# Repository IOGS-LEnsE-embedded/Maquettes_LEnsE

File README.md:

# LEnsE IOGS Maquettes
Maquettes pédagogiques du LEnsE / IOGS / France
2023

## A propos de l'Institut d'Optique et du LEnsE
Le **LEnsE**, ***Laboratoire d'Enseignement Expérimental***, forme au métier de l’ingénieur en photonique par la pratique : travaux pratiques, projets encadrés… Pour plus d'informations sur cette structure, dépendante de l'Institut d'Optique Graduate School, vous pouvez visiter le site officiel : [Site du LEnsE](http://lense.institutoptique.fr/)

## Maquettes pédagogiques
Le personnel du LEnsE développe des maquettes pédagogiques utilisées dans les différents travaux pratiques et projets proposés aux élèves de l'Institut d'Optique. 

Nous mettons ici à disposition l'ensemble des documents permettant la **reproduction de ces maquettes**, à savoir les plans des cartes électroniques (format Kicad et Gerber), les programmes de test et une documentation. Lorsque la maquette s'y prête, vous pourrez également trouver un sujet de TP pour des élèves de Licence à Master.

Les maquettes sont triées selon les **catégories suivantes** :

- Electronique analogique (répertoire *Elec\_Analog* )
- Electronique numérique / embarquée (répertoire *Elec\_Num\_Emb* )

## Utilisation
Vous trouverez dans les différents répertoires des maquettes, les éléments suivants (selon la nature de la maquette) :

- répertoire **carte** : le projet Kicad (schéma, PCB) et les fichiers gerber associés
- document **brochage** : le brochage de la carte (format PDF et PPTX)
- document **documentation** : une notice d'utilisation de la maquette
- répertoire **progs** : des programmes de tests (dans le cas de maquettes pour l'électronique embarquée)

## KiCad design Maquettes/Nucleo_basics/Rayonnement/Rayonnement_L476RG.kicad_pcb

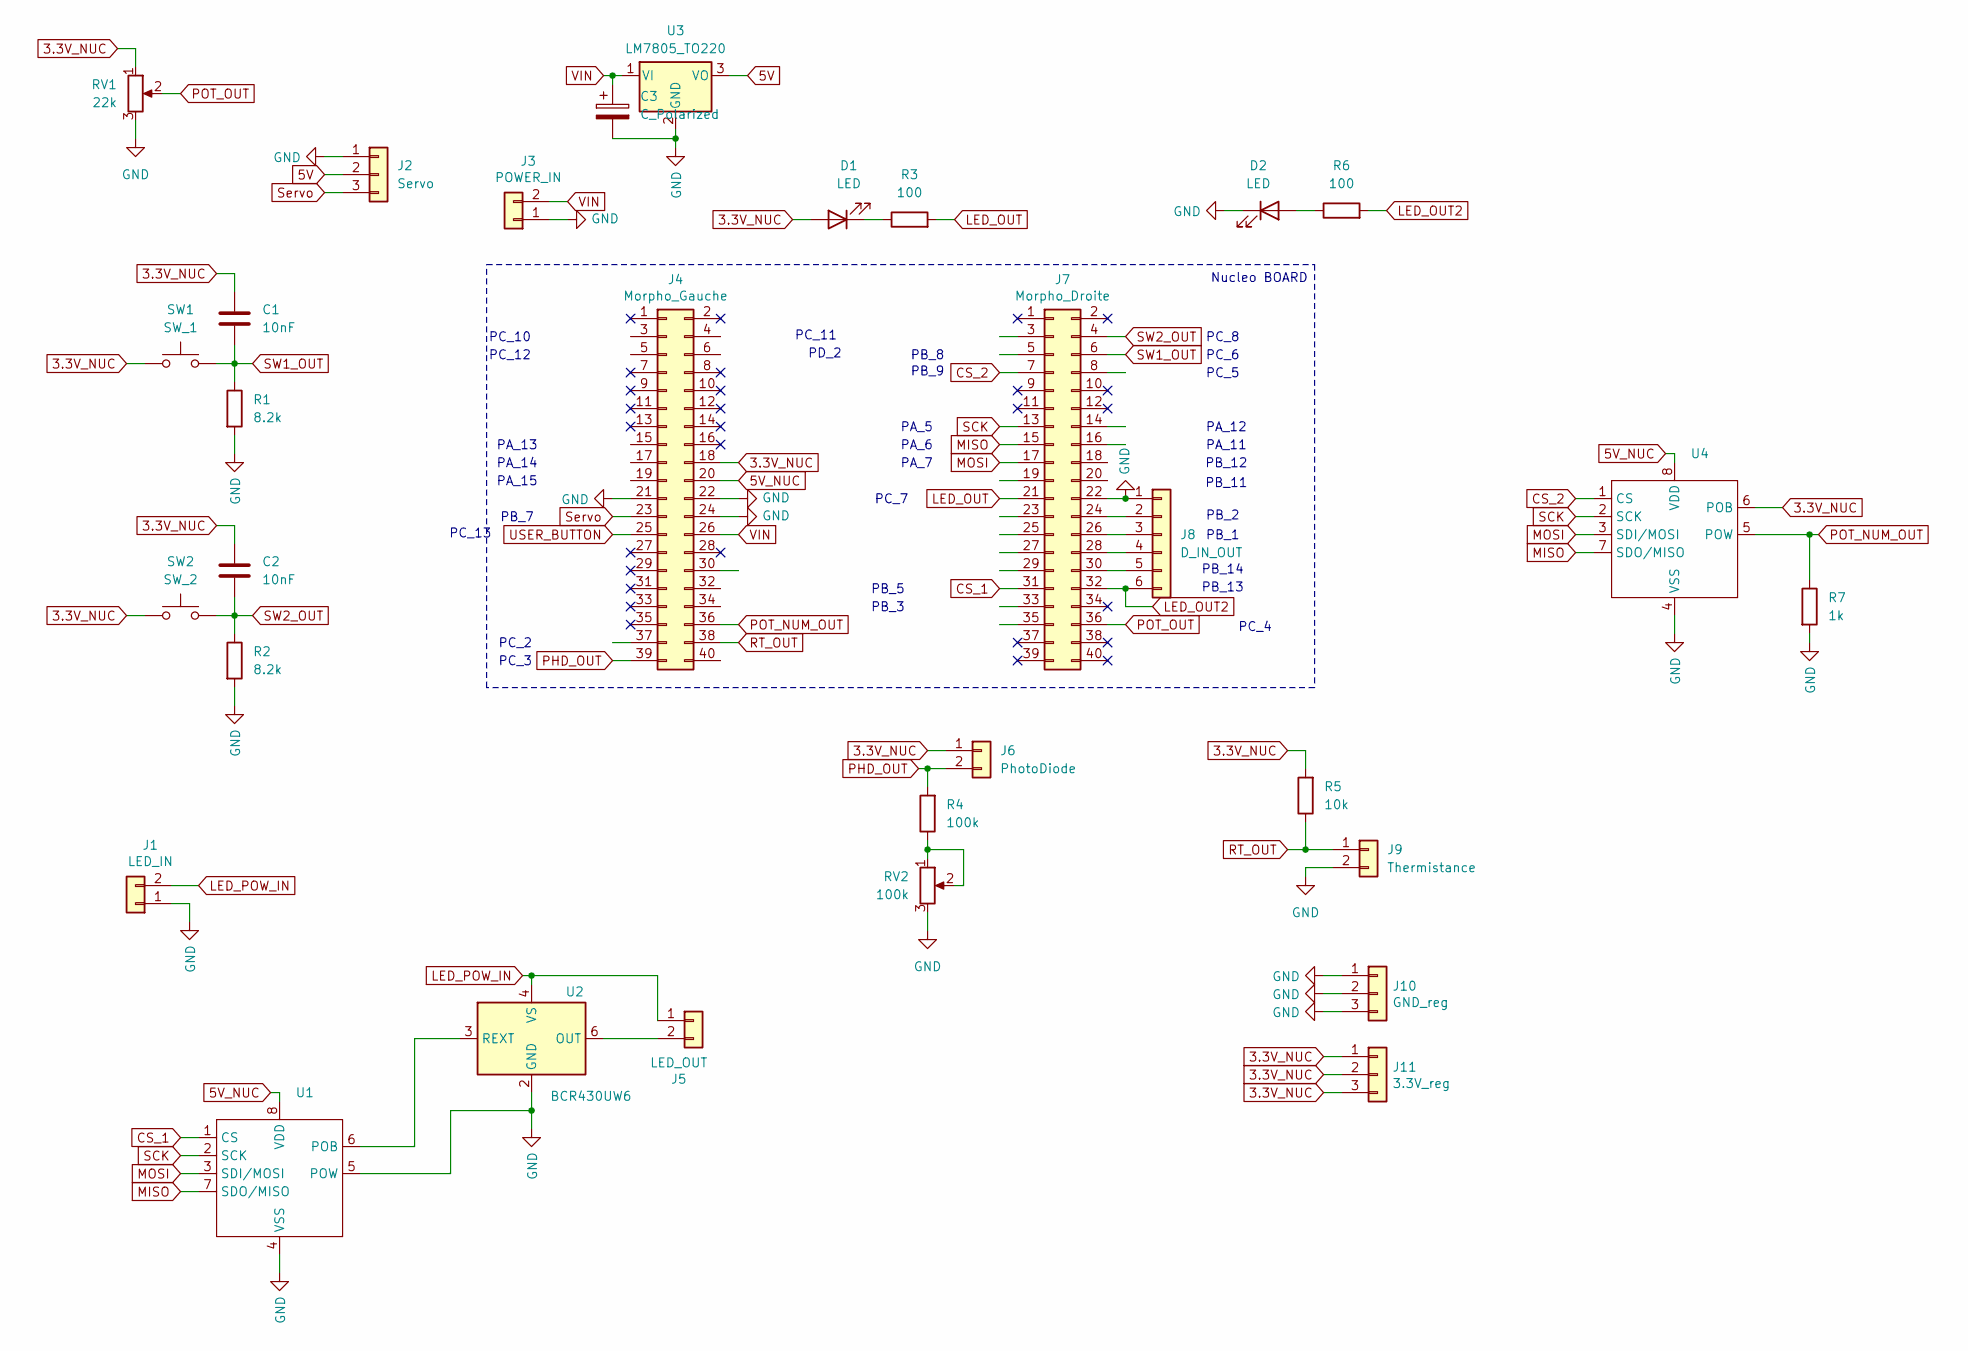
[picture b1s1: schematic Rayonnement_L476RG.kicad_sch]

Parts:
C1, C2: 10nF; C_Rect_L7.0mm_W3.5mm_P5.00mm
C3: C_Polarized; CP_Radial_D6.3mm_P2.50mm
D1, D2: LED; LED_D3.0mm_Clear
J1: LED_IN; TerminalBlock_Phoenix_MKDS-3-2-5.08_1x02_P5.08mm_Horizontal
J2: Servo; PinSocket_1x03_P2.54mm_Vertical
J3: POWER_IN; TerminalBlock_Phoenix_MKDS-3-2-5.08_1x02_P5.08mm_Horizontal
J4: Morpho_Gauche; PinHeader_2x20_P2.54mm_Vertical
J5: LED_OUT; TerminalBlock_Phoenix_MKDS-3-2-5.08_1x02_P5.08mm_Horizontal
J6: PhotoDiode; PinHeader_1x02_P2.54mm_Vertical
J7: Morpho_Droite; PinHeader_2x20_P2.54mm_Vertical
J8: D_IN_OUT; PinSocket_1x06_P2.54mm_Vertical
J9: Thermistance; PinHeader_1x02_P2.54mm_Vertical
J10: GND_reg; PinHeader_1x03_P2.54mm_Vertical
J11: 3.3V_reg; PinHeader_1x03_P2.54mm_Vertical
R1, R2: 8.2k; R_Axial_DIN0207_L6.3mm_D2.5mm_P10.16mm_Horizontal
R3, R6: 100; R_Axial_DIN0207_L6.3mm_D2.5mm_P10.16mm_Horizontal
R4: 100k; R_Axial_DIN0207_L6.3mm_D2.5mm_P10.16mm_Horizontal
R5: 10k; R_Axial_DIN0207_L6.3mm_D2.5mm_P10.16mm_Horizontal
R7: 1k; R_Axial_DIN0207_L6.3mm_D2.5mm_P10.16mm_Horizontal
RV1: 22k; Potentiometer_Bourns_3386P_Vertical
RV2: 100k; Potentiometer_Bourns_3386P_Vertical
SW1: SW_1; Switch
SW2: SW_2; Switch
U1, U4: DIP-8_W7.62mm_LongPads
U2: BCR430UW6; SC-74-6_1.55x2.9mm_P0.95mm
U3: LM7805_TO220; TO-220-3_Vertical

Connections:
3.3V_NUC: C1.1, C2.1, D1.2 (A), J4.18, J6.1, J11.1, J11.2, J11.3, R5.2, RV1.1, SW1.1, SW2.1, U4.6 (POB)
5V: J2.2, U3.3 (VO)
5V_NUC: J4.20, U1.8 (VDD), U4.8 (VDD)
CS_1: J7.31, U1.1 (CS)
CS_2: J7.7, U4.1 (CS)
GND: C3.2, D2.1 (K), J1.1, J2.1, J3.1, J4.21, J4.22, J4.24, J7.22, J8.1, J9.2, J10.1, J10.2, J10.3, R1.2, R2.2, R7.2, RV1.3, RV2.3, U1.4 (VSS), U1.5 (POW), U2.2 (GND), U3.2 (GND), U4.4 (VSS)
LED_OUT: J7.21, R3.2
LED_OUT2: J7.32, J8.6, R6.2
LED_POW_IN: J1.2, J5.1, U2.4 (VS)
MISO: J7.15, U1.7 (SDO/MISO), U4.7 (SDO/MISO)
MOSI: J7.17, U1.3 (SDI/MOSI), U4.3 (SDI/MOSI)
unnamed: D1.1 (K), R3.1
unnamed: D2.2 (A), R6.1
unnamed: J5.2, U2.6 (OUT)
unnamed: J7.24, J8.2
unnamed: J7.26, J8.3
unnamed: J7.28, J8.4
unnamed: J7.30, J8.5
unnamed: R4.1, RV2.1, RV2.2
unnamed: U1.6 (POB), U2.3 (REXT)
PHD_OUT: J4.39, J6.2, R4.2
POT_NUM_OUT: J4.36, R7.1, U4.5 (POW)
POT_OUT: J7.36, RV1.2
RT_OUT: J4.38, J9.1, R5.1
SCK: J7.13, U1.2 (SCK), U4.2 (SCK)
SW1_OUT: C1.2, J7.6, R1.1, SW1.2
SW2_OUT: C2.2, J7.4, R2.1, SW2.2
Servo: J2.3, J4.23
USER_BUTTON: J4.25
VIN: C3.1, J3.2, J4.26, U3.1 (VI)

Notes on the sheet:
PA_12
PC_2
PB_8
PA_7
PC_8
PC_11
PB_3
PA_5
PB_13
PA_14
PB_11
PC_7
PB_9
PC_5
PB_2
PC_12
PB_14
PC_13
PD_2
PA_15
PC_10
PA_11
PC_4
PA_6
PA_13
PB_7
Nucleo BOARD
PB_12
PC_3
PB_1
PC_6
PB_5

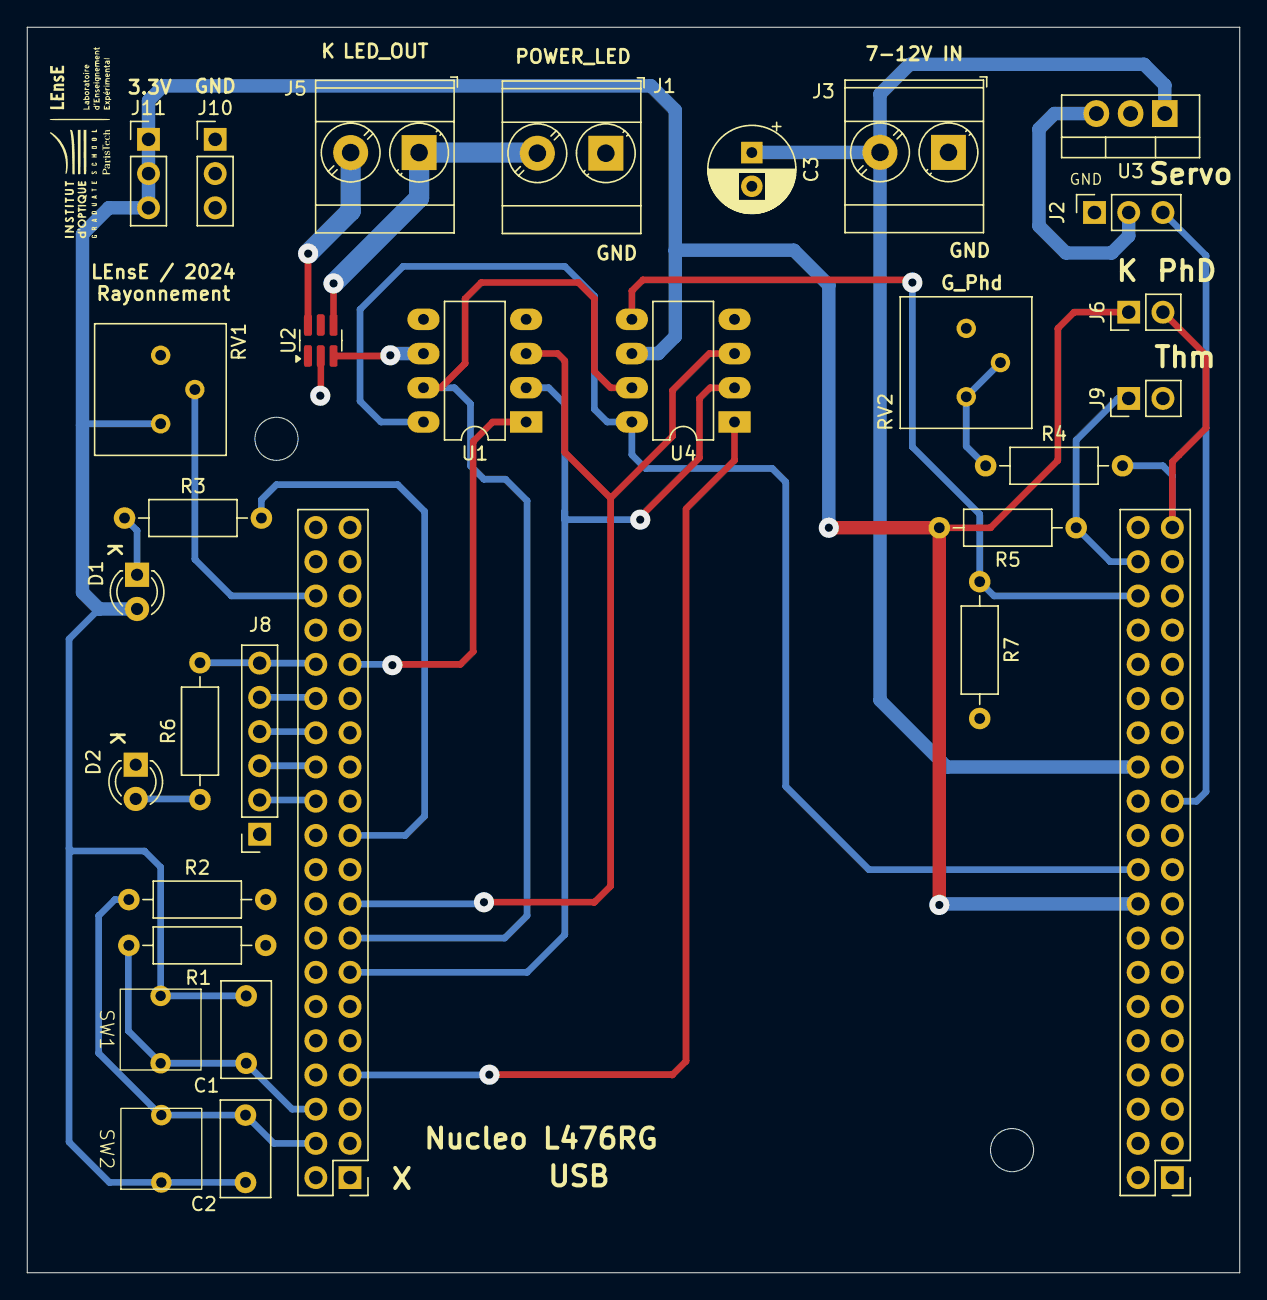
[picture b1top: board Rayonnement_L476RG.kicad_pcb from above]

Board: 2 copper layers, 90.0 x 92.5 mm, 31 parts (0 on the bottom side), 29 nets.

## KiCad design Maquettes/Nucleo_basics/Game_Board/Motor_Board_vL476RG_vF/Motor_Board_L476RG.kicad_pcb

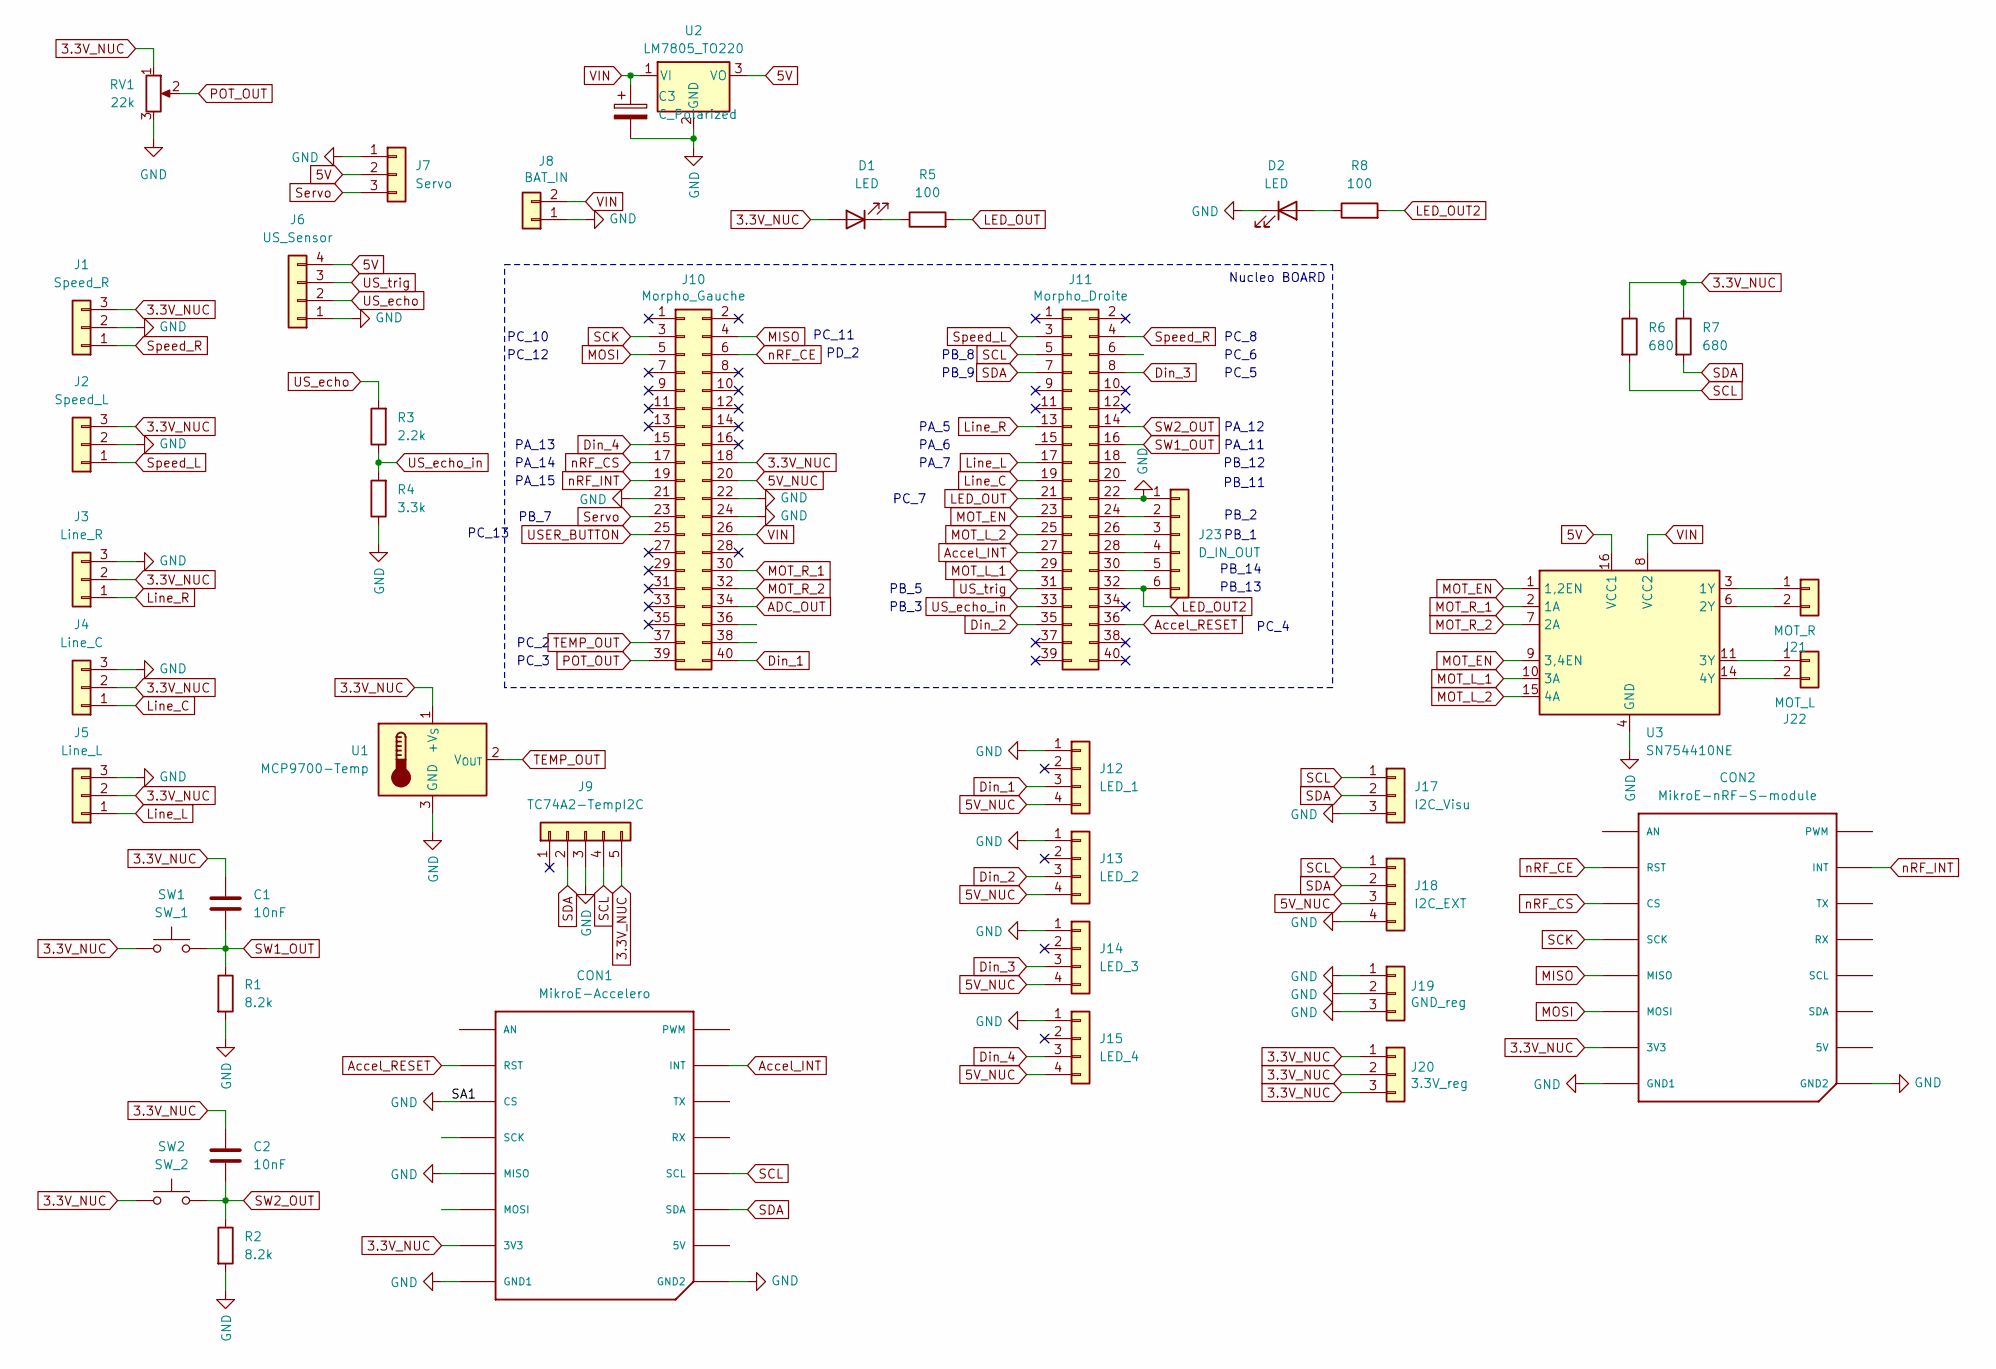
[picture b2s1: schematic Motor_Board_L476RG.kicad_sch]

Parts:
C1, C2: 10nF; C_Rect_L7.0mm_W3.5mm_P5.00mm
C3: C_Polarized; CP_Radial_D6.3mm_P2.50mm
CON1: MikroE-Accelero; MIKROBUS_MODULE_CONN
CON2: MikroE-nRF-S-module; MIKROBUS_MODULE_CONN
D1, D2: LED; LED_D3.0mm_Clear
J1: Speed_R; PinSocket_1x03_P2.54mm_Horizontal
J2: Speed_L; PinSocket_1x03_P2.54mm_Horizontal
J3: Line_R; PinSocket_1x03_P2.54mm_Horizontal
J4: Line_C; PinSocket_1x03_P2.54mm_Horizontal
J5: Line_L; PinSocket_1x03_P2.54mm_Horizontal
J6: US_Sensor; PinSocket_1x04_P2.54mm_Vertical
J7: Servo; PinSocket_1x03_P2.54mm_Horizontal
J8: BAT_IN; TerminalBlock_Phoenix_MKDS-3-2-5.08_1x02_P5.08mm_Horizontal
J9: TC74A2-TempI2C; TO-220-5_Vertical
J10: Morpho_Gauche; PinHeader_2x20_P2.54mm_Vertical
J11: Morpho_Droite; PinHeader_2x20_P2.54mm_Vertical
J12: LED_1; PinSocket_1x04_P2.54mm_Horizontal
J13: LED_2; PinSocket_1x04_P2.54mm_Horizontal
J14: LED_3; PinSocket_1x04_P2.54mm_Horizontal
J15: LED_4; PinSocket_1x04_P2.54mm_Horizontal
J17: I2C_Visu; PinSocket_1x03_P2.54mm_Vertical
J18: I2C_EXT; PinSocket_1x04_P2.54mm_Vertical
J19: GND_reg; PinHeader_1x03_P2.54mm_Vertical
J20: 3.3V_reg; PinHeader_1x03_P2.54mm_Vertical
J21: MOT_R; TerminalBlock_Phoenix_MKDS-3-2-5.08_1x02_P5.08mm_Horizontal
J22: MOT_L; TerminalBlock_Phoenix_MKDS-3-2-5.08_1x02_P5.08mm_Horizontal
J23: D_IN_OUT; PinSocket_1x06_P2.54mm_Vertical
R1, R2: 8.2k; R_Axial_DIN0207_L6.3mm_D2.5mm_P10.16mm_Horizontal
R3: 2.2k; R_Axial_DIN0207_L6.3mm_D2.5mm_P10.16mm_Horizontal
R4: 3.3k; R_Axial_DIN0207_L6.3mm_D2.5mm_P10.16mm_Horizontal
R5, R8: 100; R_Axial_DIN0207_L6.3mm_D2.5mm_P10.16mm_Horizontal
R6, R7: 680; R_Axial_DIN0207_L6.3mm_D2.5mm_P10.16mm_Horizontal
RV1: 22k; Potentiometer_Bourns_3386P_Vertical
SW1: SW_1; Switch
SW2: SW_2; Switch
U1: MCP9700-Temp; TO-92_Inline
U2: LM7805_TO220; TO-220-3_Vertical
U3: SN754410NE; DIP-16_W7.62mm

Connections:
3.3V_NUC: C1.1, C2.1, CON1.P7 (3V3), CON2.P7 (3V3), D1.2 (A), J1.3, J2.3, J3.2, J4.2, J5.2, J9.5, J10.18, J20.1, J20.2, J20.3, R6.1, R7.1, RV1.1, SW1.1, SW2.1, U1.1 (+V_{S})
5V: J6.4, J7.2, U2.3 (VO), U3.16 (VCC1)
5V_NUC: J10.20, J12.4, J13.4, J14.4, J15.4, J18.3
ADC_OUT: J10.34
Accel_INT: CON1.P15 (INT), J11.27
Accel_RESET: CON1.P2 (RST), J11.36
Din_1: J10.40, J12.3
Din_2: J11.35, J13.3
Din_3: J11.8, J14.3
Din_4: J10.15, J15.3
GND: C3.2, CON1.P3 (CS), CON1.P5 (MISO), CON1.P8 (GND1), CON1.P9 (GND2), CON2.P8 (GND1), CON2.P9 (GND2), D2.1 (K), J1.2, J2.2, J3.3, J4.3, J5.3, J6.1, J7.1, J8.1, J9.3, J10.21, J10.22, J10.24, J11.22, J12.1, J13.1, J14.1, J15.1, J17.3, J18.4, J19.1, J19.2, J19.3, J23.1, R1.2, R2.2, R4.1, RV1.3, U1.3 (GND), U2.2 (GND), U3.4 (GND), U3.5 (GND), U3.12 (GND), U3.13 (GND)
LED_OUT: J11.21, R5.2
LED_OUT2: J11.32, J23.6, R8.2
Line_C: J4.1, J11.19
Line_L: J5.1, J11.17
Line_R: J3.1, J11.13
MISO: CON2.P5 (MISO), J10.4
MOSI: CON2.P6 (MOSI), J10.5
MOT_EN: J11.23, U3.1 (1,2EN), U3.9 (3,4EN)
MOT_L_1: J11.29, U3.10 (3A)
MOT_L_2: J11.25, U3.15 (4A)
MOT_R_1: J10.30, U3.2 (1A)
MOT_R_2: J10.32, U3.7 (2A)
unnamed: D1.1 (K), R5.1
unnamed: D2.2 (A), R8.1
unnamed: J11.24, J23.2
unnamed: J11.26, J23.3
unnamed: J11.28, J23.4
unnamed: J11.30, J23.5
unnamed: J21.1, U3.3 (1Y)
unnamed: J21.2, U3.6 (2Y)
unnamed: J22.1, U3.11 (3Y)
unnamed: J22.2, U3.14 (4Y)
POT_OUT: J10.39, RV1.2
SCK: CON2.P4 (SCK), J10.3
SCL: CON1.P12 (SCL), J9.4, J11.5, J17.1, J18.1, R6.2
SDA: CON1.P11 (SDA), J9.2, J11.7, J17.2, J18.2, R7.2
SW1_OUT: C1.2, J11.16, R1.1, SW1.2
SW2_OUT: C2.2, J11.14, R2.1, SW2.2
Servo: J7.3, J10.23
Speed_L: J2.1, J11.3
Speed_R: J1.1, J11.4
TEMP_OUT: J10.37, U1.2 (V_{OUT})
USER_BUTTON: J10.25
US_echo: J6.2, R3.2
US_echo_in: J11.33, R3.1, R4.2
US_trig: J6.3, J11.31
VIN: C3.1, J8.2, J10.26, U2.1 (VI), U3.8 (VCC2)
nRF_CE: CON2.P2 (RST), J10.6
nRF_CS: CON2.P3 (CS), J10.17
nRF_INT: CON2.P15 (INT), J10.19

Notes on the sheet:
PA_12
PC_2
PB_8
PA_7
PC_8
PC_11
PB_3
PA_5
PB_13
PA_14
PB_11
PC_7
PB_9
PC_5
PB_2
PC_12
PB_14
PC_13
PD_2
PA_15
PC_10
PA_11
PC_4
PA_6
PA_13
PB_7
Nucleo BOARD
PB_12
PC_3
PB_1
PC_6
PB_5

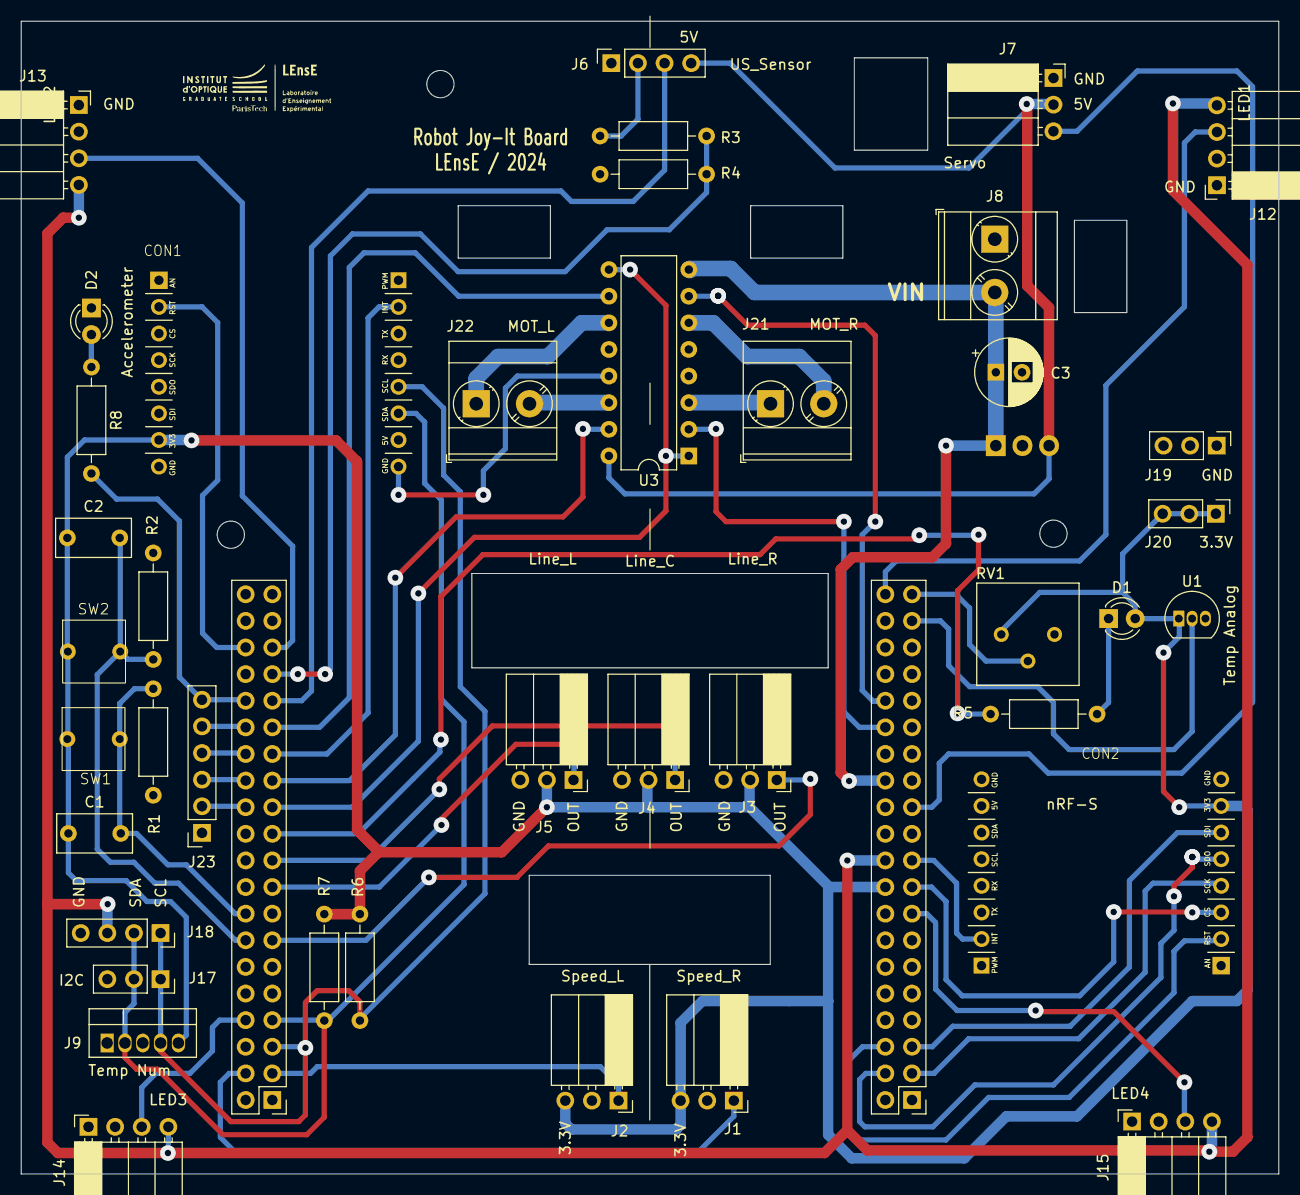
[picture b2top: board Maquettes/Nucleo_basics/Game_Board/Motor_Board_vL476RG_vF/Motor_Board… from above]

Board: 2 copper layers, 120.0 x 110.0 mm, 43 parts (1 on the bottom side), 49 nets.

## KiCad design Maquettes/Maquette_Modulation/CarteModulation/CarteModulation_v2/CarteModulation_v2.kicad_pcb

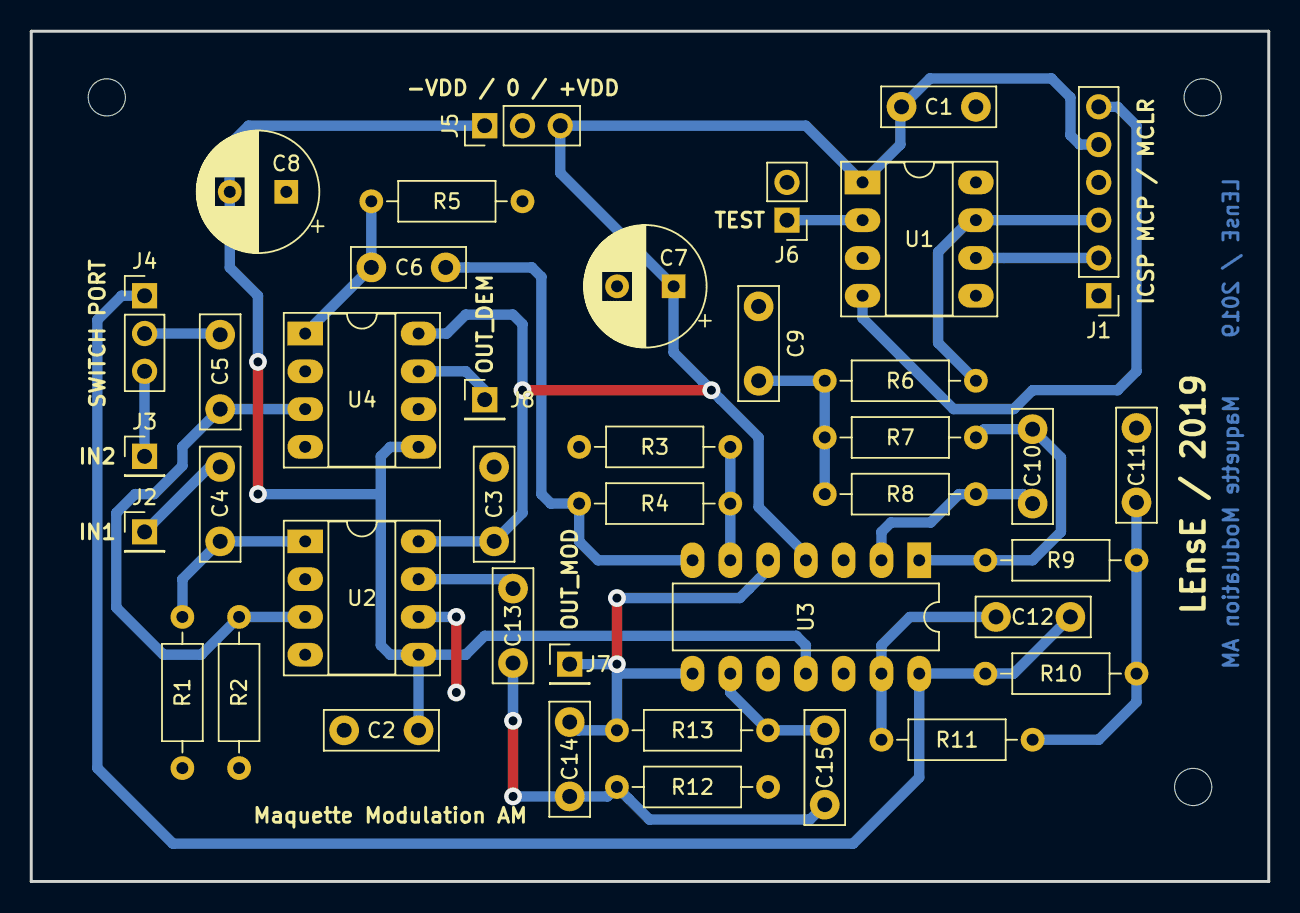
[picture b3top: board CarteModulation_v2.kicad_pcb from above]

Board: 2 copper layers, 83.2 x 57.1 mm, 41 parts (0 on the bottom side), 26 nets.

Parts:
C1, C2, C3, C4, C5, C6: 100n; C_Disc_D7.5mm_W2.5mm_P5.00mm
C7, C8: 10uF; CP_Radial_D8.0mm_P3.80mm
C9, C11: 4.7n; C_Disc_D7.5mm_W2.5mm_P5.00mm
C10, C12: 1n; C_Disc_D7.5mm_W2.5mm_P5.00mm
C13, C14, C15: 2.2n; C_Disc_D7.5mm_W2.5mm_P5.00mm
J1: ICSP; PinHeader_1x06_P2.54mm_Vertical
J2: IN1_I; PinHeader_1x01_P2.54mm_Vertical
J3: IN2_I; PinHeader_1x01_P2.54mm_Vertical
J4: CHOIX_IN; PinHeader_1x03_P2.54mm_Vertical
J5: ALIM; PinHeader_1x03_P2.54mm_Vertical
J6: TEST; PinHeader_1x02_P2.54mm_Vertical
J7: OUT_MOD; PinHeader_1x01_P2.54mm_Vertical
J8: OUT_DEMODU; PinHeader_1x01_P2.54mm_Vertical
R1, R2, R5: 100k; R_Axial_DIN0207_L6.3mm_D2.5mm_P10.16mm_Horizontal
R3, R12: 2.7k; R_Axial_DIN0207_L6.3mm_D2.5mm_P10.16mm_Horizontal
R4, R13: 27k; R_Axial_DIN0207_L6.3mm_D2.5mm_P10.16mm_Horizontal
R6, R9: 3.9k; R_Axial_DIN0207_L6.3mm_D2.5mm_P10.16mm_Horizontal
R7, R8, R10, R11: 3.3k; R_Axial_DIN0207_L6.3mm_D2.5mm_P10.16mm_Horizontal
U1: PIC12F1501-IP; DIP-8_W7.62mm_Socket_LongPads
U2, U4: AD633_DIP; DIP-8_W7.62mm_Socket_LongPads
U3: TL084; DIP-14_W7.62mm_LongPads
eREF**: MountingHole_2.5mm

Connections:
-VDD: C2.1, C8.2, J5.1, U2.5, U3.11, U4.5
GND: C1.1, C2.2, C3.1, C7.2, C8.1, C9.1, C11.1, J1.4, J5.2, J6.2, R1.2, R2.2, R3.2, R5.2, R12.1, U1.3, U1.8, U2.2, U2.4, U2.6, U3.3, U3.10, U3.12, U4.2, U4.4, U4.6
ICSP_MCLR: J1.6, U1.4
ICSP_PGC: J1.2, U1.6
ICSP_PGD: J1.3, R6.2, U1.7
IN1: C4.2, J2.1
IN2: J3.1, J4.3
IN2_CH: C5.2, J4.2
IN2_CH_FIL: C5.1, R2.1, U2.3, U4.3
MOD_AMP: C6.2, R4.1, U3.7
unnamed: C4.1, R1.1, U2.1
unnamed: C6.1, R5.1, U4.1
unnamed: C9.2, R6.1, R7.1, R8.2
unnamed: C10.1, R7.2, R9.2, U3.1
unnamed: C10.2, R8.1, U3.2
unnamed: C11.2, R9.1, R10.1, R11.2
unnamed: C12.2, R11.1, U3.13
unnamed: C13.1, C14.2, C15.1, R12.2
unnamed: C15.2, R13.1, U3.9
unnamed: R3.1, R4.2, U3.6
OUT2_FILT: C12.1, J4.1, R10.2, U3.14
OUT_DEMOD: J8.1, U4.7
OUT_MODUL: C14.1, J7.1, R13.2, U3.5, U3.8
OUT_MODUL_M: C13.2, U2.7
TEST_OUT: J6.1, U1.2
VDD: C1.2, C3.2, C7.1, J1.5, J5.3, U1.1, U2.8, U3.4, U4.8

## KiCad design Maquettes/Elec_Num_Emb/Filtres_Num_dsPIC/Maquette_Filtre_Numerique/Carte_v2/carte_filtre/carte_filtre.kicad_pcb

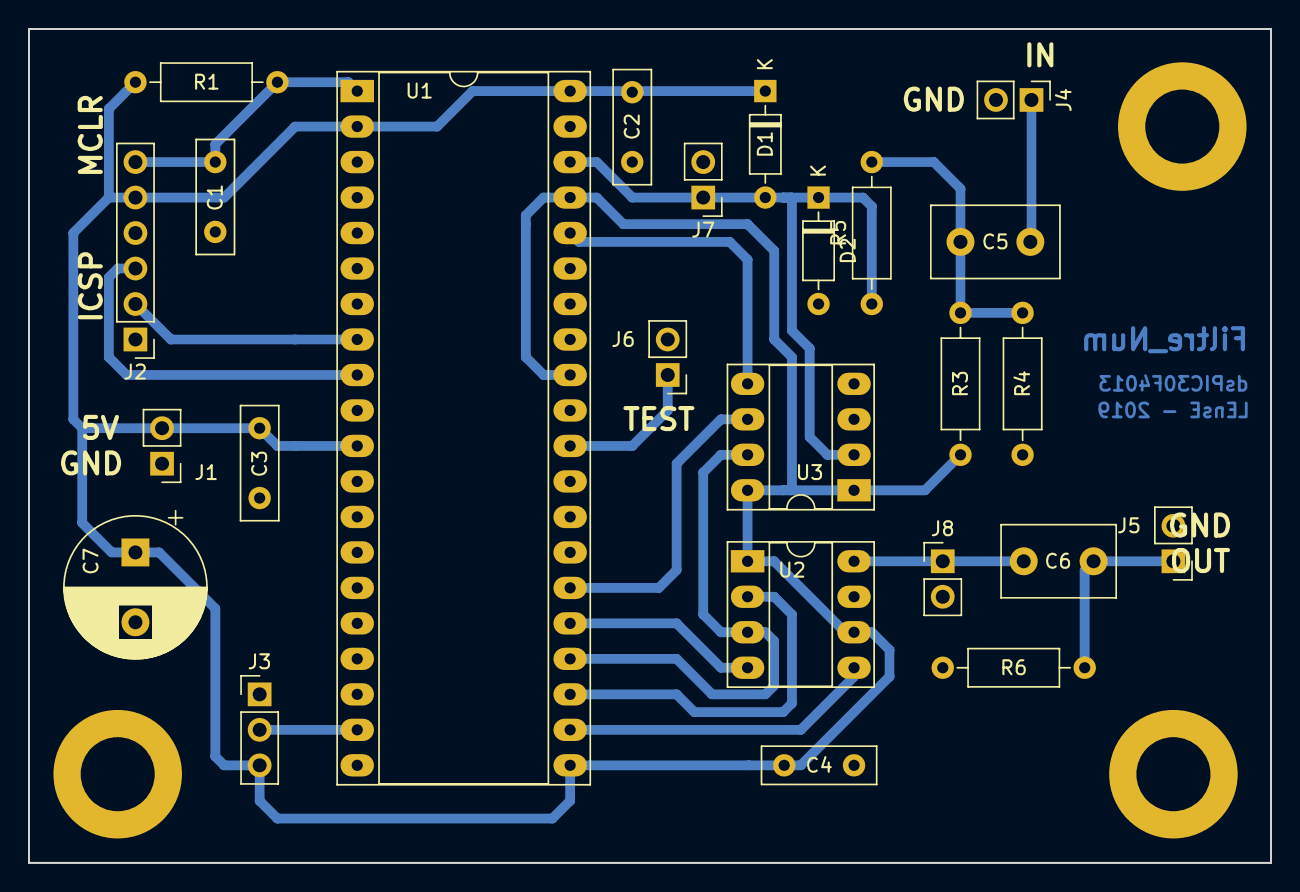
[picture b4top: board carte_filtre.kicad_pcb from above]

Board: 2 copper layers, 88.9 x 59.7 mm, 26 parts (0 on the bottom side), 18 nets.

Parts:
C1: 68pF; C_Disc_D8.0mm_W2.5mm_P5.00mm
C2, C3, C4: 100nF; C_Disc_D8.0mm_W2.5mm_P5.00mm
C5: 330nF; C_Disc_D9.0mm_W5.0mm_P5.00mm
C6: 1u; C_Disc_D8.0mm_W5.0mm_P5.00mm
C7: CP; CP_Radial_D10.0mm_P5.00mm
D1, D2: 1N4148; D_DO-35_SOD27_P7.62mm_Horizontal
H: MountingHole_5.3mm_M5_DIN965_Pad
J1: ALIM; PinHeader_1x02_P2.54mm_Vertical
J2: ICSP_MICROCHIP; PinHeader_1x06_P2.54mm_Vertical
J3: CHOIX_FILTRE_SUIVEUR; PinHeader_1x03_P2.54mm_Vertical
J4: ANALOG_IN_; PinHeader_1x02_P2.54mm_Vertical
J5: FILTERED_OUT; PinHeader_1x02_P2.54mm_Vertical
J6: TEST_OUT; PinHeader_1x02_P2.54mm_Vertical
J7: TEST_IN_; PinHeader_1x02_P2.54mm_Vertical
J8: TEST_OUT_*; PinHeader_1x02_P2.54mm_Vertical
R1, R6: 10k; R_Axial_DIN0207_L6.3mm_D2.5mm_P10.16mm_Horizontal
R3, R4: 100k; R_Axial_DIN0207_L6.3mm_D2.5mm_P10.16mm_Horizontal
R5: 1k; R_Axial_DIN0207_L6.3mm_D2.5mm_P10.16mm_Horizontal
U1: DSPIC30F3014-20E_P; DIP-40_W15.24mm_Socket_LongPads
U2: MCP4921; DIP-8_W7.62mm_Socket_LongPads
U3: MCP3201; DIP-8_W7.62mm_Socket_LongPads

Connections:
ADC_CS: U1.36, U3.5
ANALOG_IN: D1.2, D2.1, J7.1, R5.1, U1.38, U3.2
ANALOG_IN_NOT_FILTERED: C5.2, J4.1
ANALOG_OUT: C6.1, J5.1, R6.2
ANALOG_OUT_MOY: C6.2, J8.1, U2.8
CHOIX_IN: J3.2, U1.19
DAC_CS: U1.23, U2.2
DAC_LD: U1.22, U2.5
GND: C1.1, C2.2, C3.2, C4.2, C7.2, D2.2, J1.1, J2.4, J3.1, J4.2, J5.2, J6.2, J7.2, J8.2, R4.2, R6.1, U1.3, U1.12, U1.20, U1.31, U1.39, U2.7, U3.3, U3.4
MCLR: C1.2, J2.6, R1.1, U1.1
MISO_SPI: U1.26, U3.6
MOSI_SPI: U1.25, U2.4
unnamed: C5.1, R3.2, R4.1, R5.2
PGC: J2.2, U1.8
PGD: J2.3, U1.9
SCK_SPI: U1.24, U2.3, U3.7
TEST: J6.1, U1.30
VDD: C2.1, C3.1, C4.1, C7.1, D1.1, J1.2, J2.5, J3.3, R1.2, R3.1, U1.2, U1.11, U1.21, U1.32, U1.37, U1.40, U2.1, U2.6, U3.1, U3.8

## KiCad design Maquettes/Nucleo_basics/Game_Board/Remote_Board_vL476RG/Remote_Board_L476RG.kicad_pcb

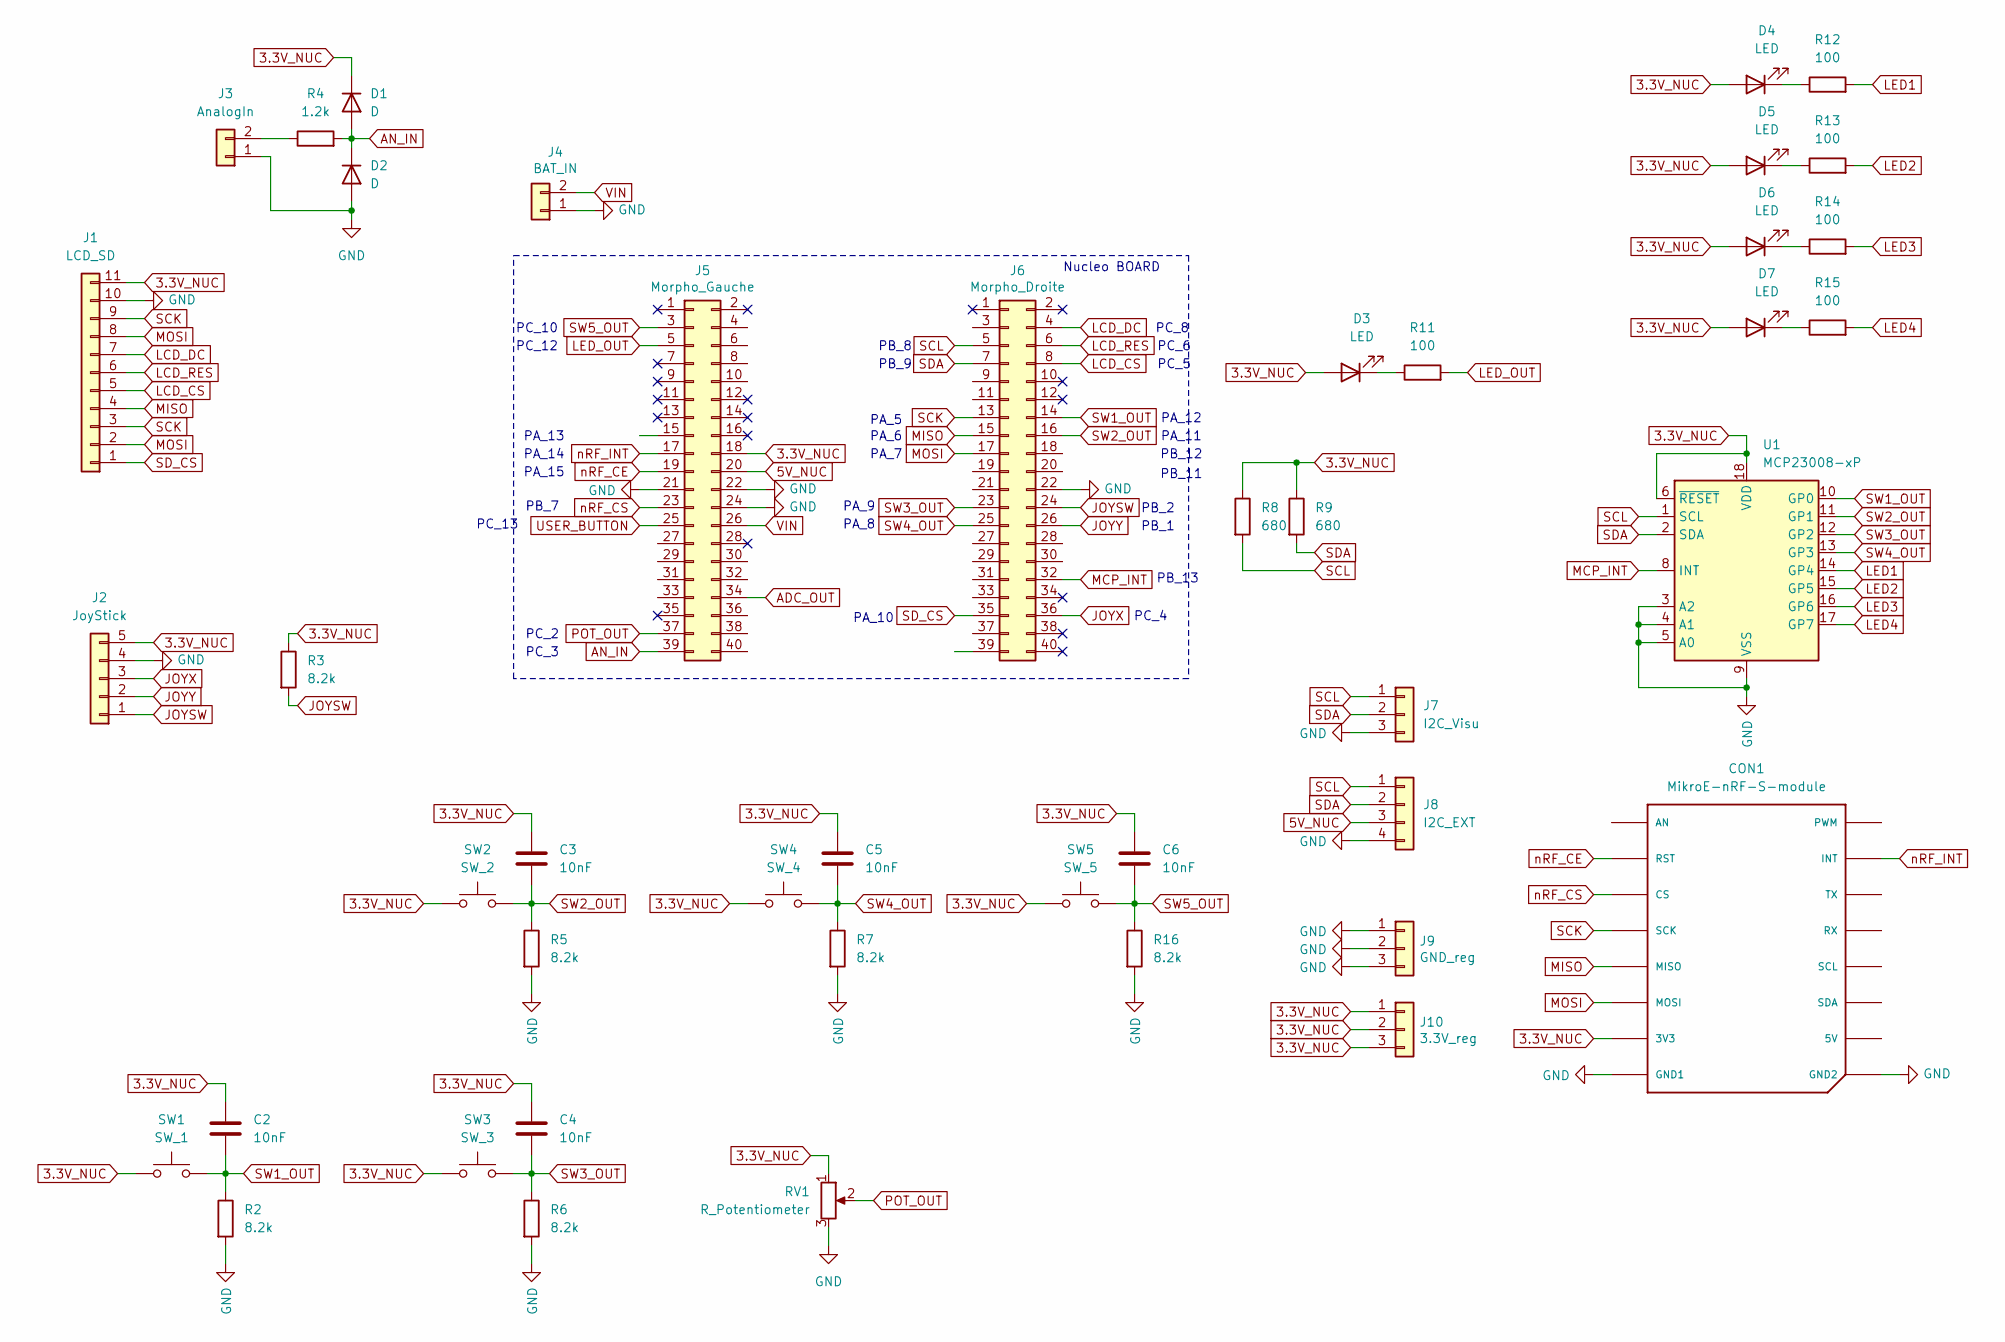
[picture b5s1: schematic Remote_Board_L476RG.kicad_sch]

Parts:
C2, C3, C4, C5, C6: 10nF; C_Rect_L7.0mm_W3.5mm_P5.00mm
CON1: MikroE-nRF-S-module; MIKROBUS_MODULE_CONN
D1, D2: D; D_DO-35_SOD27_P7.62mm_Horizontal
D3, D4, D5, D6, D7: LED; LED_D3.0mm_Clear
J1: LCD_SD; PinSocket_1x11_P2.54mm_Horizontal
J2: JoyStick; PinSocket_1x05_P2.54mm_Horizontal
J3: AnalogIn; PinSocket_1x02_P2.54mm_Horizontal
J4: BAT_IN; TerminalBlock_Phoenix_MKDS-3-2-5.08_1x02_P5.08mm_Horizontal
J5: Morpho_Gauche; PinHeader_2x20_P2.54mm_Vertical
J6: Morpho_Droite; PinHeader_2x20_P2.54mm_Vertical
J7: I2C_Visu; PinSocket_1x03_P2.54mm_Vertical
J8: I2C_EXT; PinSocket_1x04_P2.54mm_Horizontal
J9: GND_reg; PinHeader_1x03_P2.54mm_Vertical
J10: 3.3V_reg; PinHeader_1x03_P2.54mm_Vertical
R2, R3, R5, R6, R7, R16: 8.2k; R_Axial_DIN0207_L6.3mm_D2.5mm_P10.16mm_Horizontal
R4: 1.2k; R_Axial_DIN0207_L6.3mm_D2.5mm_P10.16mm_Horizontal
R8, R9: 680; R_Axial_DIN0207_L6.3mm_D2.5mm_P10.16mm_Horizontal
R11, R12, R13, R14, R15: 100; R_Axial_DIN0207_L6.3mm_D2.5mm_P10.16mm_Horizontal
RV1: R_Potentiometer; Potentiometer_Vishay_T73YP_Vertical
SW1: SW_1; Switch
SW2: SW_2; Switch
SW3: SW_3; Switch
SW4: SW_4; Switch
SW5: SW_5; Switch
U1: MCP23008-xP; DIP-18_W7.62mm

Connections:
3.3V_NUC: C2.1, C3.1, C4.1, C5.1, C6.1, CON1.P7 (3V3), D1.1 (K), D3.2 (A), D4.2 (A), D5.2 (A), D6.2 (A), D7.2 (A), J1.11, J2.5, J5.18, J10.1, J10.2, J10.3, R3.1, R8.1, R9.1, RV1.1, SW1.1, SW2.1, SW3.1, SW4.1, SW5.1, U1.6 (~RESET), U1.18 (VDD)
5V_NUC: J5.20, J8.3
ADC_OUT: J5.34
AN_IN: D1.2 (A), D2.1 (K), J5.39, R4.2
GND: CON1.P8 (GND1), CON1.P9 (GND2), D2.2 (A), J1.10, J2.4, J3.1, J4.1, J5.21, J5.22, J5.24, J6.22, J7.3, J8.4, J9.1, J9.2, J9.3, R2.2, R5.2, R6.2, R7.2, R16.2, RV1.3, U1.3 (A2), U1.4 (A1), U1.5 (A0), U1.9 (VSS)
JOYSW: J2.1, J6.24, R3.2
JOYX: J2.3, J6.36
JOYY: J2.2, J6.26
LCD_CS: J1.5, J6.8
LCD_DC: J1.7, J6.4
LCD_RES: J1.6, J6.6
LED1: R12.2, U1.14 (GP4)
LED2: R13.2, U1.15 (GP5)
LED3: R14.2, U1.16 (GP6)
LED4: R15.2, U1.17 (GP7)
LED_OUT: J5.5, R11.2
MCP_INT: J6.32, U1.8 (INT)
MISO: CON1.P5 (MISO), J1.4, J6.15
MOSI: CON1.P6 (MOSI), J1.2, J1.8, J6.17
unnamed: D3.1 (K), R11.1
unnamed: D4.1 (K), R12.1
unnamed: D5.1 (K), R13.1
unnamed: D6.1 (K), R14.1
unnamed: D7.1 (K), R15.1
unnamed: J3.2, R4.1
POT_OUT: J5.37, RV1.2
SCK: CON1.P4 (SCK), J1.3, J1.9, J6.13
SCL: J6.5, J7.1, J8.1, R8.2, U1.1 (SCL)
SDA: J6.7, J7.2, J8.2, R9.2, U1.2 (SDA)
SD_CS: J1.1, J6.35
SW1_OUT: C2.2, J6.14, R2.1, SW1.2, U1.10 (GP0)
SW2_OUT: C3.2, J6.16, R5.1, SW2.2, U1.11 (GP1)
SW3_OUT: C4.2, J6.23, R6.1, SW3.2, U1.12 (GP2)
SW4_OUT: C5.2, J6.25, R7.1, SW4.2, U1.13 (GP3)
SW5_OUT: C6.2, J5.3, R16.1, SW5.2
USER_BUTTON: J5.25
VIN: J4.2, J5.26
nRF_CE: CON1.P2 (RST), J5.19
nRF_CS: CON1.P3 (CS), J5.23
nRF_INT: CON1.P15 (INT), J5.17

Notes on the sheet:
PA_12
PC_2
PB_8
PA_7
PC_8
PA_5
PB_13
PA_14
PB_11
PB_9
PA_9
PC_5
PB_2
PC_12
PC_13
PA_8
PA_10
PA_15
PC_10
PA_11
PC_4
PA_6
PA_13
Nucleo BOARD
PB_12
PC_3
PB_1
PB_7
PC_6
